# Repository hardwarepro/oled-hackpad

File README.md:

##  A's Hackpad

### Description

This is a custom macropad that has 4 buttons and is controlled by a XIAO RP2040 as my main MCU. It also has an EC11 encoder for customizable actions like volume control. The 4 keys can be set to do whatever actions you want, but mine are set up as key 1 to open Gmail, key 2 takes a screenshot on Windows, key 3 holds down shift, key 4 saves a file while my EC11 controls my device's volume.

### Firmware

This custom macropad’s firmware was written in KMK, which is easy to be changed and very easy to flash to the XIAO RP2040

### BOM

|Through-hole XIAO-RP2040  |x1  |
|--|--|
|SK6812MINI LED's | x2 |
|EC11 Rotary Encoder| x1 |
|M3x16mm screws|--|
|Blank DSA keycaps  |x4  |
|MX switches  | x4 |
|||

#### Photos

This is the case I built for my macropad!

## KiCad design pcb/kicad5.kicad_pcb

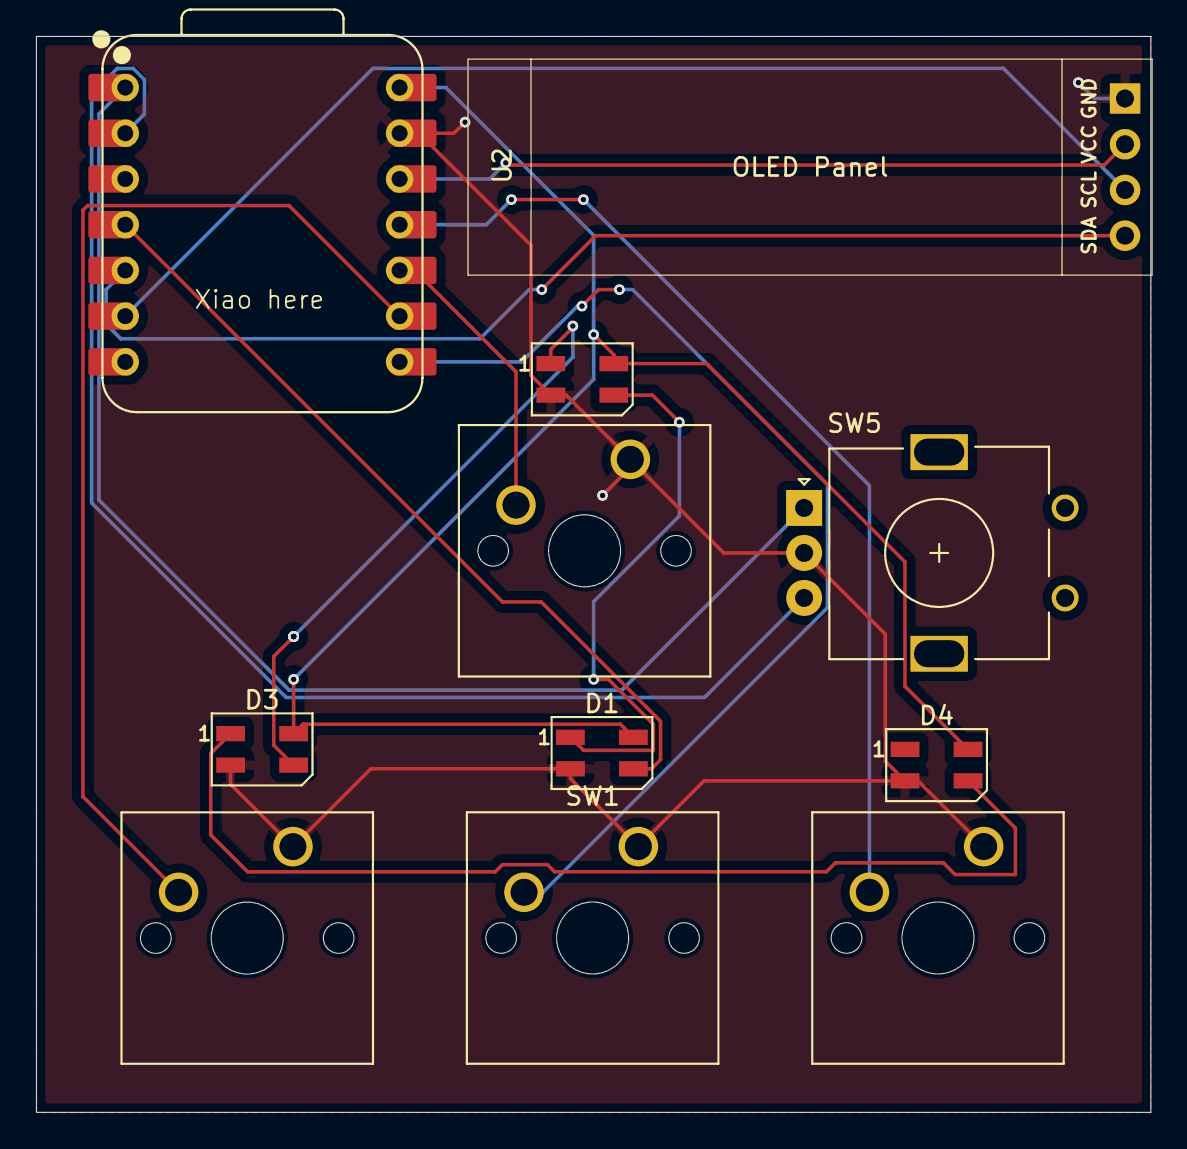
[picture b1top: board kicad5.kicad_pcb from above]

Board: 2 copper layers, 61.9 x 59.8 mm, 11 parts (0 on the bottom side), 15 nets.

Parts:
D1, D2, D3, D4: SK6812MINI; LED_SK6812MINI_PLCC4_3.5x3.5mm_P1.75mm
SW1, SW2, SW3, SW4: SW_Push; SW_Cherry_MX_1.00u_PCB
SW5: RotaryEncoder_Switch; RotaryEncoder_Alps_EC11E_Vertical_H20mm
U1: XIAO-RP2040-DIP
U2: SSD1306; SSD1306-0.91-OLED-4pin-128x32

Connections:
+3.3V: U1.12 (3V3), U2.2
+5V: D1.4 (VDD), D2.4 (VDD), D3.4 (VDD), D4.4 (VDD), U1.14 (VBUS)
GND: D1.2 (VSS), D2.2 (VSS), D3.2 (VSS), D4.2 (VSS), SW1.1, SW2.1, SW3.1, SW4.1, SW5.C, U1.13 (GND), U2.1
unnamed: D1.3 (DIN), U1.4 (GPIO29/ADC3/A3)
unnamed: D1.1 (DOUT), D2.3 (DIN)
unnamed: D2.1 (DOUT), D3.3 (DIN)
unnamed: D3.1 (DOUT), D4.3 (DIN)
unnamed: SW1.2, U1.8 (GPIO1/RX)
unnamed: SW2.2, U1.9 (GPIO2/SCK)
unnamed: SW4.2, U1.11 (GPIO3/MOSI)
unnamed: SW3.2, U1.10 (GPIO4/MISO)
unnamed: U1.5 (GPIO6/SDA), U2.4
unnamed: U1.6 (GPIO7/SCL), U2.3
unnamed: SW5.A, U1.1 (GPIO26/ADC0/A0)
unnamed: SW5.B, U1.2 (GPIO27/ADC1/A1)

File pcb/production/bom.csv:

Designator,Footprint,Quantity,Value,LCSC Part #
"D1, D2, D3, D4",LED_SK6812MINI_PLCC4_3.5x3.5mm_P1.75mm,4,SK6812MINI,
"SW1, SW2, SW3, SW4",SW_Cherry_MX_1.00u_PCB,4,SW_Push,
SW5,RotaryEncoder_Alps_EC11E_Vertical_H20mm,1,RotaryEncoder_Switch,
U1,XIAO-RP2040-DIP,1,XIAO-RP2040-DIP,
U2,SSD1306-0.91-OLED-4pin-128x32,1,SSD1306,

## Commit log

2025-06-10 Finished schematic
2025-06-10 added ec11
2025-06-10 PCB routing is done
2025-06-11 Added case model
2025-06-11 Added most of the prod files
2025-06-11 Added the rest of the files ie. firmware and README
2025-06-11 Added README images
2025-06-11 Cleanup used files
2025-06-11 Added the BOM
2025-06-17 chnges
2025-06-17 Help fix some weird traces
2025-06-17 Changes final
